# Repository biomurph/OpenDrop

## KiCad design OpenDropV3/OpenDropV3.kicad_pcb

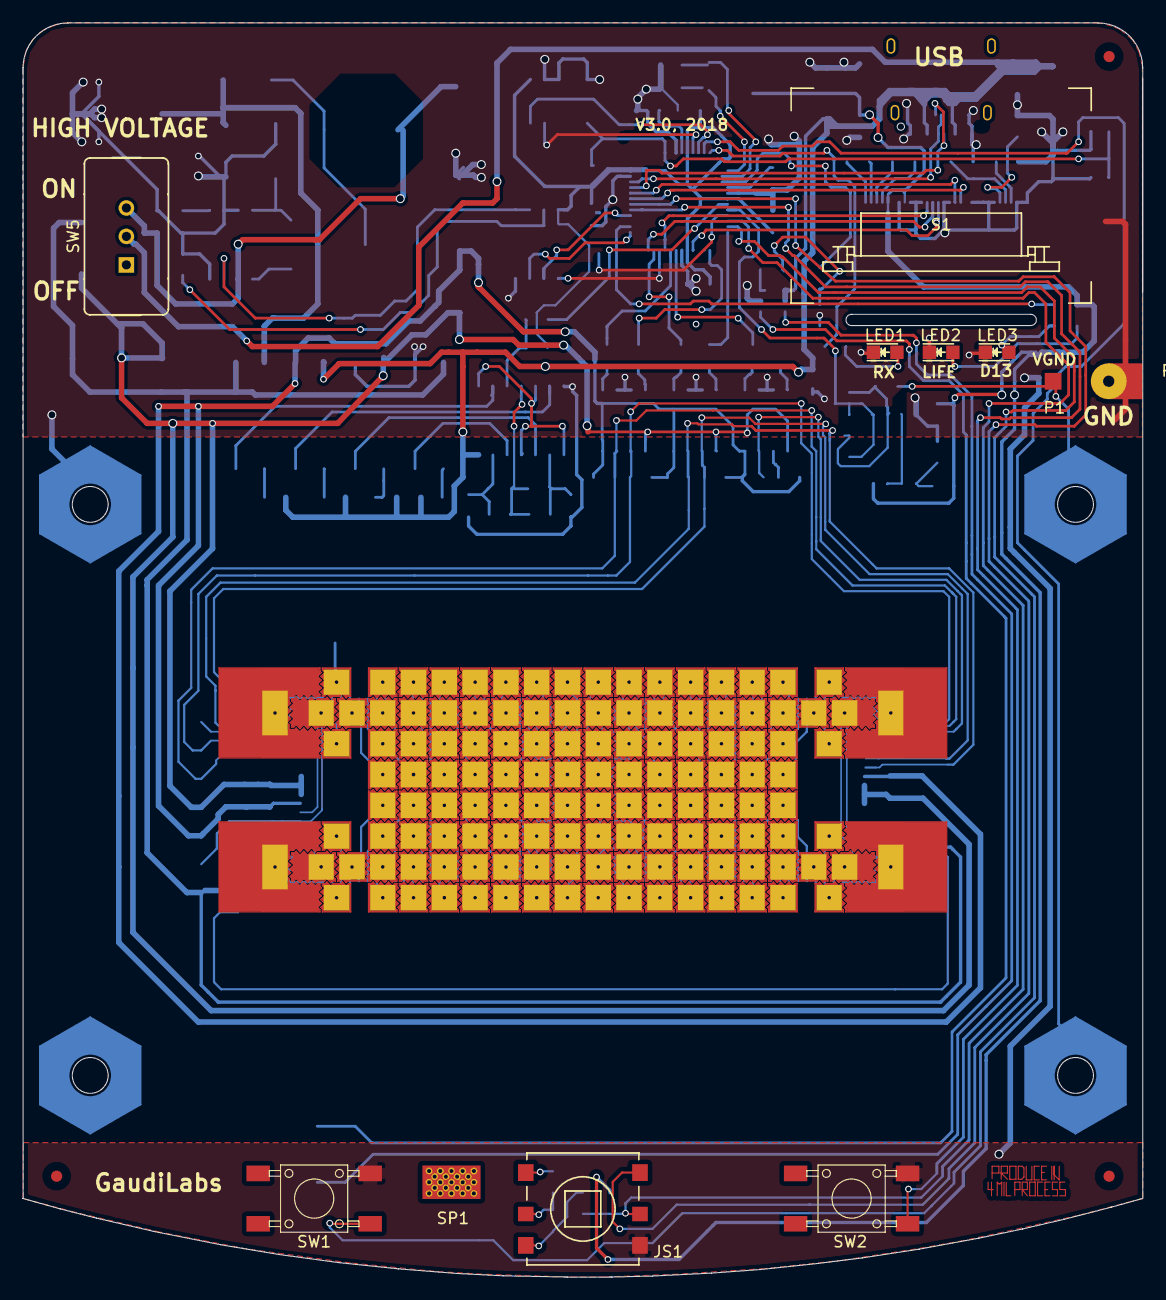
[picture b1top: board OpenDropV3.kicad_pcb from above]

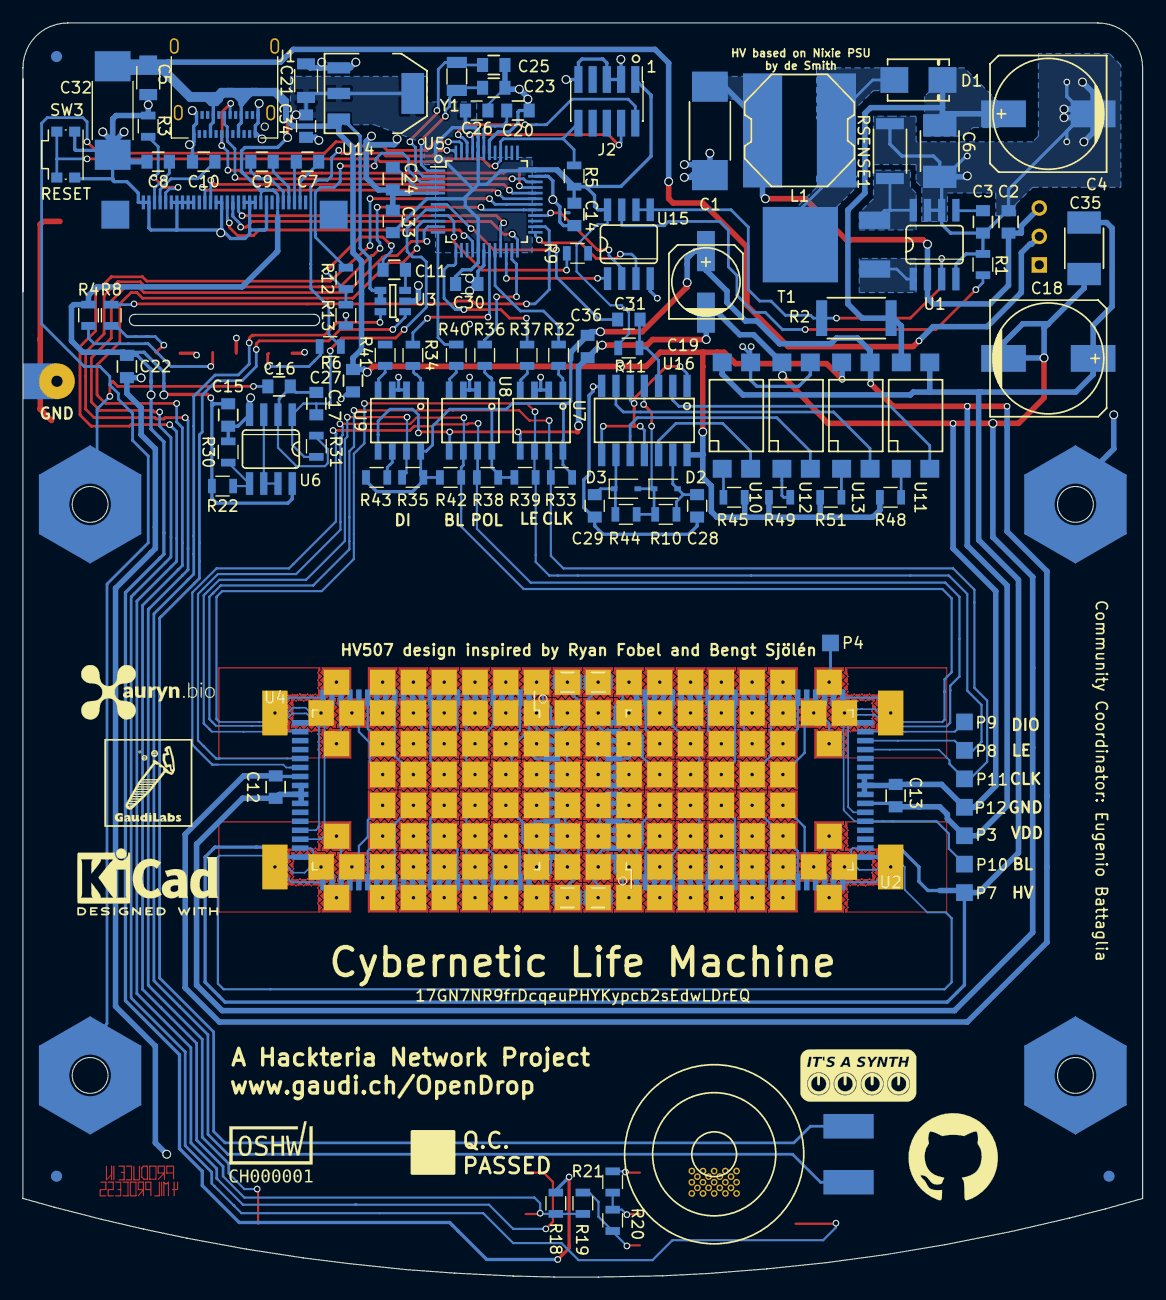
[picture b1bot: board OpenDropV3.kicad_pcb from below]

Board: 2 copper layers, 100.0 x 112.0 mm, 257 parts (110 on the bottom side), 223 nets.

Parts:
C1: 100uF, 35V; R_2512_HandSoldering
C2, C3, C12, C13, C14, C22, C26, C30, C33, C34, C36: 100nF; C_0805
C4, C18: 4u7, 250V; c_elec_10x10
C5, C21: 10uF; C_1206
C6, C35: 100nF, 250V; C_1913
C7, C9, C11, C15, C16, C20, C24, C27: 1uF; C_0805
C8, C10: 2.2uF; C_0805
C17: 1pF; C_0805
C19: 22uF, 50V; c_elec_6.3x5.8
C23, C25: 22pF; C_0805
C28, C29: 3.3nF; C_0805
C31: 220nF; C_0805
C32: 100uF,35V; R_2512_HandSoldering
D1: ES2F; DO-214AA
D2, D3: 1N4148; D_SOD-323
FLUXL_1_1, FLUXL_1_8, FLUXL_16_1, FLUXL_16_8: FX; FLUXPAD_2_75_4MIL_4_5_res3
FLUXL_1_2, FLUXL_1_7, FLUXL_16_2, FLUXL_16_7: FX; FLUXPAD_2_75_4MIL_4_5_res1
FLUXL_1_3, FLUXL_1_6, FLUXL_16_3, FLUXL_16_6: FX; FLUXPAD_2_75_4MIL_4_5_res2
FLUXL_1_4, FLUXL_1_5, FLUXL_16_4, FLUXL_16_5: FX; FLUXPAD_2_75_4MIL_4_5_res4
FLUXL_1_4b1, FLUXL_1_5b1, FLUXL_16_4b1, FLUXL_16_5b1: FX; FLUXPAD_2_75_4MIL_4_5_res5
FLUXL_2_1, FLUXL_15_8: FX; FLUXPAD_2_75_4MIL_4_5_topleft
FLUXL_2_2, FLUXL_2_7, FLUXL_3_2, FLUXL_3_3, FLUXL_3_4, FLUXL_3_5, FLUXL_3_6, FLUXL_3_7, FLUXL_4_2, FLUXL_4_3, FLUXL_4_4, FLUXL_4_5, FLUXL_4_6, FLUXL_4_7, FLUXL_5_2, FLUXL_5_3, FLUXL_5_4, FLUXL_5_5, FLUXL_5_6, FLUXL_5_7, FLUXL_6_2, FLUXL_6_3, FLUXL_6_4, FLUXL_6_5, FLUXL_6_6, FLUXL_6_7, FLUXL_7_2, FLUXL_7_3, FLUXL_7_4, FLUXL_7_5, FLUXL_7_6, FLUXL_7_7, FLUXL_8_2, FLUXL_8_3, FLUXL_8_4, FLUXL_8_5, FLUXL_8_6, FLUXL_8_7, FLUXL_9_2, FLUXL_9_3, FLUXL_9_4, FLUXL_9_5, FLUXL_9_6, FLUXL_9_7, FLUXL_10_2, FLUXL_10_3, FLUXL_10_4, FLUXL_10_5, FLUXL_10_6, FLUXL_10_7, FLUXL_11_2, FLUXL_11_3, FLUXL_11_4, FLUXL_11_5, FLUXL_11_6, FLUXL_11_7, FLUXL_12_2, FLUXL_12_3, FLUXL_12_4, FLUXL_12_5, FLUXL_12_6, FLUXL_12_7, FLUXL_13_2, FLUXL_13_3, FLUXL_13_4, FLUXL_13_5, FLUXL_13_6, FLUXL_13_7, FLUXL_14_2, FLUXL_14_3, FLUXL_14_4, FLUXL_14_5, FLUXL_14_6, FLUXL_14_7, FLUXL_15_2, FLUXL_15_7: FX; FLUXPAD_2_75_4MIL_4_5
FLUXL_2_3, FLUXL_2_4, FLUXL_2_5, FLUXL_2_6, FLUXL_15_3, FLUXL_15_4, FLUXL_15_5, FLUXL_15_6: FX; FLUXPAD_2_75_4MIL_4_5_side
FLUXL_2_8, FLUXL_15_1: FX; FLUXPAD_2_75_4MIL_4_5_topright
FLUXL_3_1, FLUXL_3_8, FLUXL_4_1, FLUXL_4_8, FLUXL_5_1, FLUXL_5_8, FLUXL_6_1, FLUXL_6_8, FLUXL_7_1, FLUXL_7_8, FLUXL_8_1, FLUXL_8_8, FLUXL_9_1, FLUXL_9_8, FLUXL_10_1, FLUXL_10_8, FLUXL_11_1, FLUXL_11_8, FLUXL_12_1, FLUXL_12_8, FLUXL_13_1, FLUXL_13_8, FLUXL_14_1, FLUXL_14_8: FX; FLUXPAD_2_75_4MIL_4_5_top
J1: USB_C_Receptacle; USB_C_Receptacle_Amphenol_12401610E4-2A
J2: Conn_02x05_Odd_Even; Pin_Header_Straight_2x05_Pitch1.27mm_SMD
JS1: JoystickSMD; JoystickSMD_SKQUSeries
L1: 100uH; SRN1060
LED1, LED2, LED3: LED; LED-0805
P1, P3, P7, P8, P9, P10, P11, P12: CONN_01X01; Measurement_Point_Square-SMD-Pad_Small
P2: ScrewPad4; Measurement_Point_Croki
P4: CONN_PSEUDO_AC; Measurement_Point_Square-SMD-Pad_Small
P13: ScrewPad1; MountingHolePad_3x9mm
P14: ScrewPad2; MountingHolePad_3x9mm
P15: ScrewPad3; MountingHolePad_3x9mm
P16: ScrewPad4; MountingHolePad_3x9mm
R1: 6.8k; R_0805
R2: 1M5; R_2512
R3, R9: 390k; R_0805
R4, R6, R8, R13: 390; R_0805
R5, R10, R18, R19, R20, R21, R22, R30, R44: 10k; R_0805
R7, R15, R16, R17: 10R; R_0805_HeatPad
R11: 47k; R_0805
R12, R33, R35, R38, R39, R42, R43: 2.2k; R_0805
R31: 15k; R_0805
R32, R34, R36, R37, R40, R41, R45, R48, R49, R51: 220; R_0805
RSENSE1: 0R1; R_2010
S1: OLED_DISPLAY; OLED_096_1_Flip
SP1: SPEAKER; Speaker16mm
SW1, SW2: SW_PUSH; PUSH_BUTTON_SMD
SW3: SW_PUSH; SW_SPST_KMS221GLFS
SW5: SPST; Switch_On-On
T1: TK560P60Y; D-Pak_TO252AA
U1: MAX1771ESA; SO08
U2, U4: HV507; PQFP-80_14x20mm_Pitch0.8mm
U3: PAM8301; SOT-23-6
U5: SAMD21G18B-A changed from SAML21; TQFP-48_7x7mm_Pitch0.5mm
U6: MCP6002; SO08
U7, U8, U9: HCPL0534; HCPL_Optocoupler_SMD
U10, U11, U12, U13: AQY210EH; SMD_DIP4
U14: TLV1117-33; SOT-223
U15: MCP41010; SO08
U16: 74xx14; SOIC-14_N
Y1: 32.765; Crystal_SMD_3215-2pin_3.2x1.5mm

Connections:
+3V3: C14.1, C15.1, C21.1, C22.2, C26.1, C30.1, C33.2, C34.2, J2.1, R4.1, R5.2, R11.2, R18.2, R22.1, S1.6, S1.9, U5.6, U5.17, U5.36, U5.44, U6.8, U14.2, U15.8
AC: C31.1, U5.7
AREF: C24.2, U5.4
BL: R40.2, U5.12
BL_C: P10.1, R42.1, U2.29, U4.29, U8.6
CLK: R32.2, U5.20
CLK_C: P11.1, R33.1, U2.37, U4.37, U7.7
D13: R8.1, U5.26
D+: J1.A6, J1.B6, U5.34
D-: J1.A7, J1.B7, U5.33
DI: R34.2, U5.19
DIO_B: P9.1, U2.39
DISP_CS: S1.13, U5.21
DISP_DC: S1.15, U5.16
DISP_RES: S1.14, U5.24
DISP_SCL: S1.18, U5.32
DISP_SDA: S1.19, U5.31
DI_C: R35.1, U4.26, U9.7
FEEDBACK: C17.1, R31.1, U5.8, U6.1
GND: C1.2, C2.2, C3.2, C4.2, C5.2, C6.2, C8.2, C10.2, C14.2, C15.2, C20.2, C21.2, C22.1, C23.1, C24.1, C25.1, C26.2, C27.1, C28.1, C29.1, C30.2, C32.2, C33.1, C34.1, J1.A1, J1.A12, J1.B1, J1.B12, J2.3, J2.5, J2.9, JS1.4, LED1.1, LED2.1, LED3.1, P2.1, P13.1, R1.2, R3.2, R13.2, R30.2, RSENSE1.2, S1.8, S1.10, S1.11, S1.12, S1.16, S1.17, S1.21, S1.22, S1.23, S1.24, S1.25, S1.29, S1.30, SW1.2, SW2.2, SW3.2, U1.4, U1.6, U1.7, U3.2, U5.5, U5.18, U5.35, U5.42, U6.4, U7.2, U7.3, U8.2, U8.3, U9.2, U9.3, U10.3, U12.3, U14.1, U15.4, U16.7
GND_C: C12.2, C13.2, C18.2, C19.2, C35.2, C36.2, P12.1, U2.32, U2.33, U2.34, U4.32, U4.33, U4.34, U7.5, U8.5, U9.5, U12.4
JOY: JS1.5, R18.1, R19.2, U5.10
LE: R37.2, U5.13
LE_C: P8.1, R39.1, U2.38, U4.38, U7.6
unnamed: C1.1, C2.1, L1.1, SW5.1, U1.2
unnamed: C3.1, U1.5
unnamed: C7.1, S1.2
unnamed: C7.2, S1.3
unnamed: C8.1, S1.28
unnamed: C9.1, S1.4
unnamed: C9.2, S1.5
unnamed: C10.1, S1.27
unnamed: C11.1, R12.1, R13.1
unnamed: C11.2, U3.3
unnamed: C16.1, C17.2, R31.2, U6.2
unnamed: C20.1, U5.43
unnamed: C23.2, U5.1, Y1.1
unnamed: C25.2, U5.2, Y1.2
unnamed: C28.2, D2.2, R10.2, U16.13
unnamed: C29.2, D3.1, R44.2, U16.9
unnamed: C31.2, R11.1, U16.3
unnamed: D1.2, L1.2, T1.2
unnamed: D2.1, D3.2, R10.1, R44.1, U16.4
unnamed: FLUXL_1_1.1, U2.41
unnamed: FLUXL_1_2.1, U2.44
unnamed: FLUXL_1_3.1, U2.42
unnamed: FLUXL_1_4.1, FLUXL_1_4b1.1, P4.1, U2.43
unnamed: FLUXL_1_5.1, FLUXL_1_5b1.1, U2.22
unnamed: FLUXL_1_6.1, U2.23
unnamed: FLUXL_1_7.1, U2.21
unnamed: FLUXL_1_8.1, U2.24
unnamed: FLUXL_2_1.1, U2.47
unnamed: FLUXL_2_2.1, U2.48
unnamed: FLUXL_2_3.1, U2.46
unnamed: FLUXL_2_4.1, U2.45
unnamed: FLUXL_2_5.1, U2.20
unnamed: FLUXL_2_6.1, U2.19
unnamed: FLUXL_2_7.1, U2.17
unnamed: FLUXL_2_8.1, U2.18
unnamed: FLUXL_3_1.1, U2.51
unnamed: FLUXL_3_2.1, U2.50
unnamed: FLUXL_3_3.1, U2.52
unnamed: FLUXL_3_4.1, U2.49
unnamed: FLUXL_3_5.1, U2.16
unnamed: FLUXL_3_6.1, U2.13
unnamed: FLUXL_3_7.1, U2.15
unnamed: FLUXL_3_8.1, U2.14
unnamed: FLUXL_4_1.1, U2.54
unnamed: FLUXL_4_2.1, U2.55
unnamed: FLUXL_4_3.1, U2.56
unnamed: FLUXL_4_4.1, U2.53
unnamed: FLUXL_4_5.1, U2.12
unnamed: FLUXL_4_6.1, U2.9
unnamed: FLUXL_4_7.1, U2.10
unnamed: FLUXL_4_8.1, U2.11
unnamed: FLUXL_5_1.1, U2.58
unnamed: FLUXL_5_2.1, U2.59
unnamed: FLUXL_5_3.1, U2.60
unnamed: FLUXL_5_4.1, U2.57
unnamed: FLUXL_5_5.1, U2.8
unnamed: FLUXL_5_6.1, U2.5
unnamed: FLUXL_5_7.1, U2.6
unnamed: FLUXL_5_8.1, U2.7
unnamed: FLUXL_6_1.1, U2.61
unnamed: FLUXL_6_2.1, U2.62
unnamed: FLUXL_6_3.1, U2.63
unnamed: FLUXL_6_4.1, U2.64
unnamed: FLUXL_6_5.1, U2.1
unnamed: FLUXL_6_6.1, U2.2
unnamed: FLUXL_6_7.1, U2.3
unnamed: FLUXL_6_8.1, U2.4
unnamed: FLUXL_7_1.1, U2.65
unnamed: FLUXL_7_2.1, U2.69
unnamed: FLUXL_7_3.1, U2.68
unnamed: FLUXL_7_4.1, U2.72
unnamed: FLUXL_7_5.1, U2.73
unnamed: FLUXL_7_6.1, U2.78
unnamed: FLUXL_7_7.1, U2.76
unnamed: FLUXL_7_8.1, U2.80
unnamed: FLUXL_8_1.1, U2.70
unnamed: FLUXL_8_2.1, U2.66
unnamed: FLUXL_8_3.1, U2.67
unnamed: FLUXL_8_4.1, U2.71
unnamed: FLUXL_8_5.1, U2.74
unnamed: FLUXL_8_6.1, U2.77
unnamed: FLUXL_8_7.1, U2.79
unnamed: FLUXL_8_8.1, U2.75
unnamed: FLUXL_9_1.1, U4.75
unnamed: FLUXL_9_2.1, U4.79
unnamed: FLUXL_9_3.1, U4.77
unnamed: FLUXL_9_4.1, U4.74
unnamed: FLUXL_9_5.1, U4.71
unnamed: FLUXL_9_6.1, U4.67
unnamed: FLUXL_9_7.1, U4.66
unnamed: FLUXL_9_8.1, U4.70
unnamed: FLUXL_10_1.1, U4.80
unnamed: FLUXL_10_2.1, U4.76
unnamed: FLUXL_10_3.1, U4.78
unnamed: FLUXL_10_4.1, U4.73
unnamed: FLUXL_10_5.1, U4.72
unnamed: FLUXL_10_6.1, U4.68
unnamed: FLUXL_10_7.1, U4.69
unnamed: FLUXL_10_8.1, U4.65
unnamed: FLUXL_11_1.1, U4.4
unnamed: FLUXL_11_2.1, U4.3
unnamed: FLUXL_11_3.1, U4.2
unnamed: FLUXL_11_4.1, U4.1
unnamed: FLUXL_11_5.1, U4.64
unnamed: FLUXL_11_6.1, U4.63
unnamed: FLUXL_11_7.1, U4.62
unnamed: FLUXL_11_8.1, U4.61
unnamed: FLUXL_12_1.1, U4.7
unnamed: FLUXL_12_2.1, U4.6
unnamed: FLUXL_12_3.1, U4.5
unnamed: FLUXL_12_4.1, U4.8
unnamed: FLUXL_12_5.1, U4.57
unnamed: FLUXL_12_6.1, U4.60
unnamed: FLUXL_12_7.1, U4.59
unnamed: FLUXL_12_8.1, U4.58
unnamed: FLUXL_13_1.1, U4.11
unnamed: FLUXL_13_2.1, U4.10
unnamed: FLUXL_13_3.1, U4.9
unnamed: FLUXL_13_4.1, U4.12
unnamed: FLUXL_13_5.1, U4.53
unnamed: FLUXL_13_6.1, U4.56
unnamed: FLUXL_13_7.1, U4.55
unnamed: FLUXL_13_8.1, U4.54
unnamed: FLUXL_14_1.1, U4.14
unnamed: FLUXL_14_2.1, U4.15
unnamed: FLUXL_14_3.1, U4.13
unnamed: FLUXL_14_4.1, U4.16
unnamed: FLUXL_14_5.1, U4.49
unnamed: FLUXL_14_6.1, U4.52
unnamed: FLUXL_14_7.1, U4.50
unnamed: FLUXL_14_8.1, U4.51
unnamed: FLUXL_15_1.1, U4.18
unnamed: FLUXL_15_2.1, U4.17
unnamed: FLUXL_15_3.1, U4.19
unnamed: FLUXL_15_4.1, U4.20
unnamed: FLUXL_15_5.1, U4.45
unnamed: FLUXL_15_6.1, U4.46
unnamed: FLUXL_15_7.1, U4.48
unnamed: FLUXL_15_8.1, U4.47
unnamed: FLUXL_16_1.1, U4.24
unnamed: FLUXL_16_2.1, U4.21
unnamed: FLUXL_16_3.1, U4.23
unnamed: FLUXL_16_4.1, FLUXL_16_4b1.1, U4.22
unnamed: FLUXL_16_5.1, FLUXL_16_5b1.1, U4.43
unnamed: FLUXL_16_6.1, U4.42
unnamed: FLUXL_16_7.1, U4.44
unnamed: FLUXL_16_8.1, U4.41
unnamed: JS1.1, R21.1
unnamed: JS1.2, R20.1, R21.2
unnamed: JS1.3, R19.1, R20.2
unnamed: LED1.2, R6.2
unnamed: LED2.2, R4.2
unnamed: LED3.2, R8.2
unnamed: R1.1, R9.2, U15.7
unnamed: R2.2, U1.3, U15.5, U15.6
unnamed: R3.1, S1.26
unnamed: R22.2, R30.1, U6.5
unnamed: R32.1, U7.1
unnamed: R34.1, U9.1
unnamed: R36.1, U8.1
unnamed: R37.1, U7.4
unnamed: R40.1, U8.4
unnamed: R41.1, U9.4
unnamed: R43.1, U9.6
unnamed: R45.1, U10.1
unnamed: R48.1, U11.1
unnamed: R49.1, U12.1
unnamed: R51.1, U13.1
unnamed: RSENSE1.1, T1.3, U1.8
unnamed: SP1.1, U3.1
unnamed: SP1.2, U3.6
unnamed: T1.1, U1.1
unnamed: U2.26, U4.39
unnamed: U6.3, U6.6, U6.7
unnamed: U10.2, U16.12
unnamed: U11.2, U16.2
unnamed: U12.2, U16.10
unnamed: U13.2, U16.6
unnamed: U16.1, U16.5, U16.8, U16.11
POL: R36.2, U5.23
POL_C: R38.1, U2.30, U4.30, U8.7
RESET: J2.10, R5.1, SW3.1, U5.40
RX_LED: R6.1, U5.48
SENS_PAD: P16.1, U5.47
SPK: R12.2, U5.3
SW1: SW1.1, U5.11
SW2: SW2.1, U5.29
SW3: JS1.6, U5.30
SWCLK: J2.4, U5.45
SWDIO: J2.2, U5.46
VDD_C: C12.1, C13.1, C19.1, C36.1, P3.1, R33.2, R35.2, R38.2, R39.2, R42.2, R43.2, U2.31, U4.31, U7.8, U8.8, U9.8, U13.3
VSENS: R9.1, U5.9
V_CS: U5.22, U15.1
V_GND: C16.2, P1.1, P14.1
V_HV: C4.1, C6.1, D1.1, R2.1, U11.4
V_HV_C: C18.1, C35.1, P7.1, U2.25, U4.40, U10.4, U11.3
V_SCK: U5.28, U15.2
V_SI: U5.25, U15.3
V_USB: C5.1, C27.2, C32.1, J1.A4, J1.A9, J1.B4, J1.B9, R45.2, R48.2, R49.2, R51.2, SW5.2, U3.4, U3.5, U13.4, U14.3, U16.14

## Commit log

2018-01-28 Random changes just from firing up the project
    adjusted libraries to match my paths
2018-05-02 updated library paths
2018-05-02 added gitignore
2018-05-02 trying to resolve conflict
2018-05-02 trying this
2018-05-11 updated BOM
2018-05-17 Added dimensioning
2018-05-24 update bom
2018-05-24 updatedBOM
2018-06-12 made production files of my fork
2018-06-13 Updatee Shem and footprints
    Still needs to update the PCB design with new footprints
2018-06-17 Adjusting PCB for more room around some components
2018-06-18 Updated footprint associations
2018-06-22 Updated footprints and adjusted copper pour areas
2018-08-07 Change to pcb file
